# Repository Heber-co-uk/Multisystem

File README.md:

# Multisystem all-in-one console motherboard designed by Heber Ltd. for MiSTer and the DE10-nano FPGA platform

### [Multisystem I/O console motherboard](https://github.com/Heber-co-uk/Multisystem/Multisystem_All_in_One_PCB)
This all in one motherboard (console) is designed by Heber Ltd. and is released as open-source hardware for the MiSTer FPGA community and project. This console style motherboard provides SCART, VGA, Analog and Digital audio outputs, 128MB of SDRAM, SNAC with automatic level-shifters. Multisystem also has a built in 7 port USB 2.0 Hub. HDMI Isolation, fan connections, power switch, Ethernet, 2nd SD CARD interface and a dedicated expansion connector for various cartridges.

### [Multisystem 3D printed enclosure](https://www.printables.com/model/159379-mister-multisystem-v5-2022-classic-gaming-console-)
An open source enclosure is also available  designed for 3D printing (CC-BY-SA-4.0) commercial use license, over on Printables. Various other enclosures, modules, cartridges and expansions are also being made available all the time. Please check back for future updates and new 3D prints. 3D enclosure designed by Richard Horne @RichRap3D for Heber and the Multisystem / MiSTer project.

### Various images of the Multisystem PCB can be found [here](https://github.com/Heber-co-uk/Multisystem/images)

### A comprehensive user manual for the Multisystem can be found [here](https://github.com/Heber-co-uk/Multisystem/Manual)
Please check the manual if you have any questions about assembly and use of the Multisystem or the MiSTer FPGA project.

### [The official RTC daughter board is also supported on the Multisystem](https://github.com/MiSTer-devel/Hardware_MiSTer/tree/master/Addons/RTC)
This board provides real time clock. It's plugged into LTC connector.

### [Please support the MiSTer project and its creators & developers](https://patreon.com/FPGAMiSTer)
Please consider supporting the original creators for MiSTer and any of the FPGA Core developers over on Patreon or anywhere you can support or help them.

### [Alexey Melnikov](https://github.com/sorgelig)
The MiSTer project, electronics hardware, the Linux software and many FPGA cores would not have been possible without the dedicated efforts of the community, past projects like MiST and especially Alexey Melnikov for the porting over to the DE10-nano as MiSTer. Please support the project wherever you can.

### [MiSTer Forum](https://misterfpga.org/)
The MiSTer project forum can be found here.

### [RMC Retro - TheCave]( https://www.rmcretro.com/)
We would like to thank Neil at RMCRetro for the ongoing support of this project and many others for the Retro Gaming, classic computer and Arcade gaming communities. 

### [Heber Ltd.](https://heber.co.uk/) Heber are developing hardware for the Retro Gaming, classic computer and Arcade gaming communities. If you would like to know more, please visit our website or follow us on social media. 

## Notes
The PCB design and schematic is made in Altium, you will need to use Altium Designer v19.0 (or later) in order to view the source files. For convenience, [gerber files (*.zip)]( https://github.com/Heber-co-uk/Multisystem/Multisystem_All_in_One_PCB releases) are also included
and ready to submit to a PCB manufacturer of your choice.

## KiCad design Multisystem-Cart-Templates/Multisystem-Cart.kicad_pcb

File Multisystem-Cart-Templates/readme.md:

# Heber Expansion Cartridge templates

KiCad templates for cartridges for the Multisystem and Multisystem2 / Future Multisystems.

Schematic includes the edge connector with appropriately labelled nets.

PCB includes the edge connector and a board outline.

The Multisystem cartridge also includes a micro USB 3.0 connector, which enables SNAC cartridges to be connected to other MiSTer FPGA systems. On the Multisystem, the V_SNAC signal from the edge connector and power from the USB connector will be at 5V or 3.3V depending on the voltage setting on the Multisystem, but on other MiSTer systems, the voltage from the USB connector is always 5V even when a level shifter is used. VBUS on the edge connector is current-limited 5V from the USB current limiting IC whereas 5V on the edge connector is from the main power input protected only by the main polyfuse. Also note that the SSRX and SSTX pairs are swapped in the micro USB connector; this is because the SSRX pins at the USB end connect to SSTX at the micro USB end of the cable and vice versa.

On Multisystem 2, V_SNAC is fixed at 3.3V and the level of the signals from the system are 3.3V. We recommend designing any SNAC cartridge for 5V devices with on-board level shifters so that they will be compatible with Multisystem and Multisystem 2. The common BSS138 level shifting circuit is sufficient and the pull-ups on the system side should be connected to V_SNAC for correct signal levels on the system side regardless of the position of the 5V/3.3V switch on Multisystem.

If you wish to make your own Cartridges for the Multisystem/Multisystem2, please use this template so they will be compatible.

## Board finish
Never use HASL. Use ENIG.

All official Heber cartridges feature hard gold plating on the edge contacts to improve the long term reliability of the contacts. This is an extra cost option available from most PCB manufacturers and is quite expensive to add if you are ordering prototypes; the boards will of course work without hard gold plating, but standard gold plating will wear off the pads quickly and reduce the reliability over the long term.

## Signals 
 - USB 2.0
 - GPIO Pins (3.3v)
 - Analogue input signals (on Multisystem 2, the ADC is not fitted and these signals are instead routed to the 50W header where the ADC could be connected or the signals could be used for other things)
 - +5V unprotected (2A max)
 - +3.3V unprotected (1A max)
 - GND
 - VBUS (5V protected by USB overcurrent protection IC)
 - V_SNAC (Selectable voltage on the Multisystem board 3.3v or 5v)
 - Full SNAC/USER PORT
 - Digital Audio output
 - PWM Analogue Audio output (unfiltered)
 - RGBHV Analogue video output - various display modes & Standards.
 - Sync On Green signal

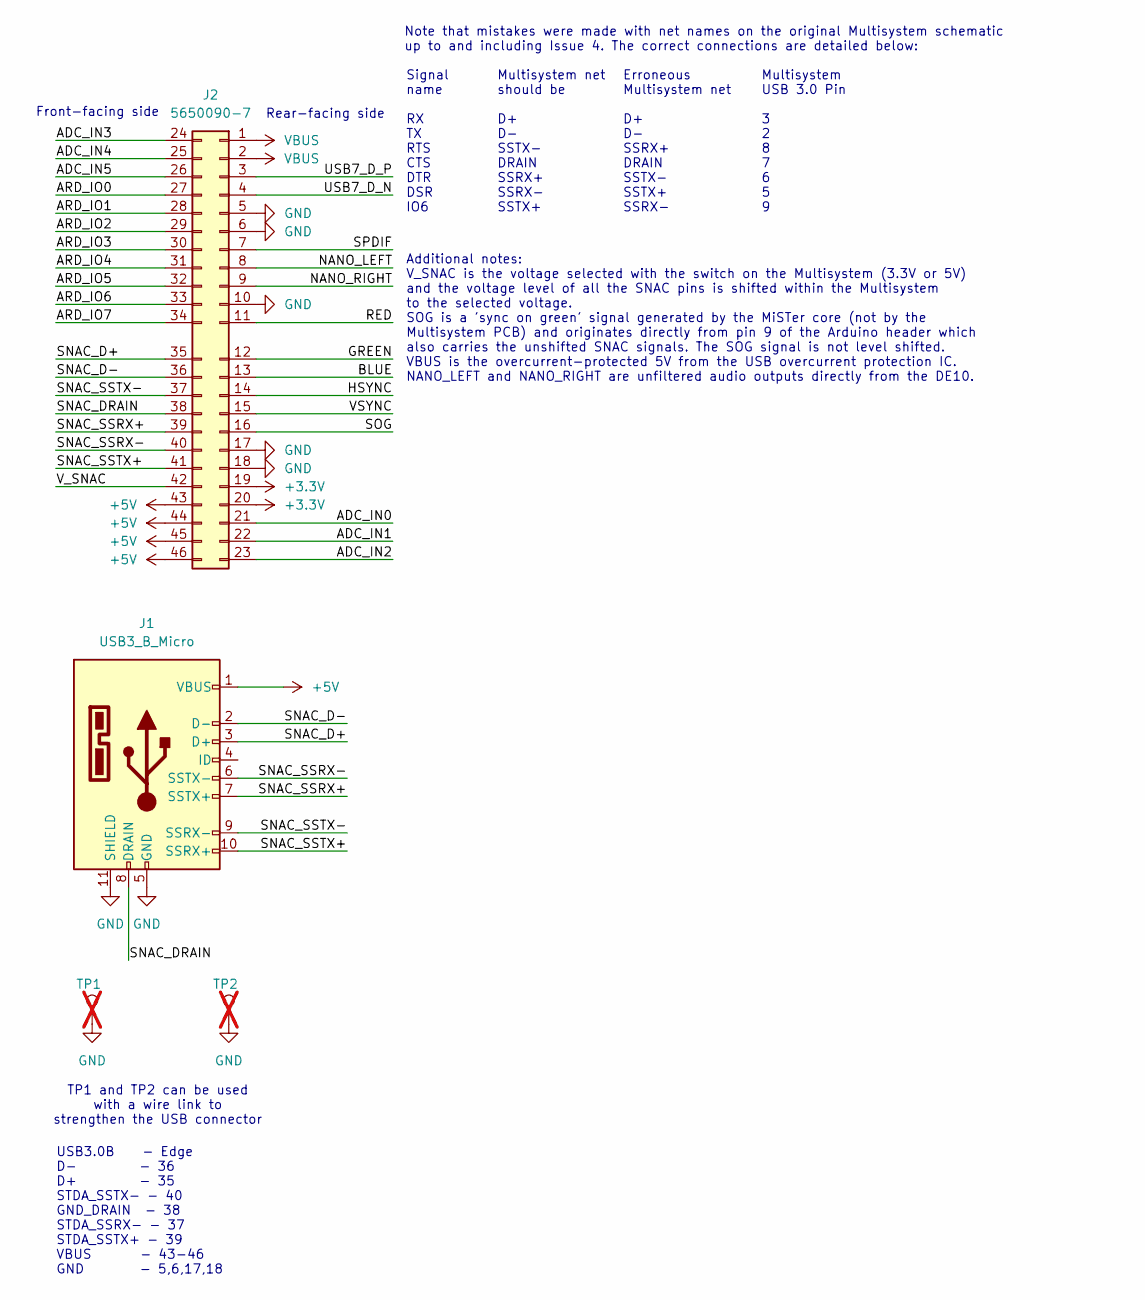
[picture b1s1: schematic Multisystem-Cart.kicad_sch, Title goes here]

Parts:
J1: USB3_B_Micro; CONN-MICRO-USB-3
J2: 5650090-7; PCI_EDGE_AMC_RISER_MULTISYSTEM
TP1, TP2: TestPoint; Pin_D1.0mm_L10.0mm; not fitted

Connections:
+3.3V: J2.19, J2.20
+5V: J1.1 (VBUS), J2.43, J2.44, J2.45, J2.46
/ADC_IN0: J2.21
/ADC_IN1: J2.22
/ADC_IN2: J2.23
/ADC_IN3: J2.24
/ADC_IN4: J2.25
/ADC_IN5: J2.26
/ARD_IO0: J2.27
/ARD_IO1: J2.28
/ARD_IO2: J2.29
/ARD_IO3: J2.30
/ARD_IO4: J2.31
/ARD_IO5: J2.32
/ARD_IO6: J2.33
/ARD_IO7: J2.34
/BLUE: J2.13
/GREEN: J2.12
/HSYNC: J2.14
/NANO_LEFT: J2.8
/NANO_RIGHT: J2.9
/RED: J2.11
/SNAC_D+: J1.3 (D+), J2.35
/SNAC_D-: J1.2 (D-), J2.36
/SNAC_DRAIN: J1.8 (DRAIN), J2.38
/SNAC_SSRX+: J1.7 (SSTX+), J2.39
/SNAC_SSRX-: J1.6 (SSTX-), J2.40
/SNAC_SSTX+: J1.10 (SSRX+), J2.41
/SNAC_SSTX-: J1.9 (SSRX-), J2.37
/SOG: J2.16
/SPDIF: J2.7
/USB7_D_N: J2.4
/USB7_D_P: J2.3
/VSYNC: J2.15
/V_SNAC: J2.42
GND: J1.5 (GND), J1.11 (SHIELD), J2.5, J2.6, J2.10, J2.17, J2.18, TP1.1, TP2.1
VBUS: J2.1, J2.2

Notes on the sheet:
Erroneous Multisystem net D+ D- SSRX+ DRAIN SSTX- SSTX+ SSRX-
USB3.0B - Edge D- - 36 D+ - 35 STDA_SSTX- - 40 GND_DRAIN - 38 STDA_SSRX- - 37 STDA_SSTX+ - 39 VBUS - 43-46 GND - 5,6,17,18
Signal name RX TX RTS CTS DTR DSR IO6
Front-facing side
TP1 and TP2 can be used with a wire link to strengthen the USB connector
Multisystem USB 3.0 Pin 3 2 8 7 6 5 9
Multisystem net should be D+ D- SSTX- DRAIN SSRX+ SSRX- SSTX+
Note that mistakes were made with net names on the original Multisystem schematic up to and including Issue 4. The correct connections are detailed below:
Rear-facing side
Additional notes: V_SNAC is the voltage selected with the switch on the Multisystem (3.3V or 5V) and the voltage level of all the SNAC pins is shifted within the Multisystem to the selected voltage. SOG is a 'sync on green' signal generated by the MiSTer core (not by the Multisystem PCB) and origin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

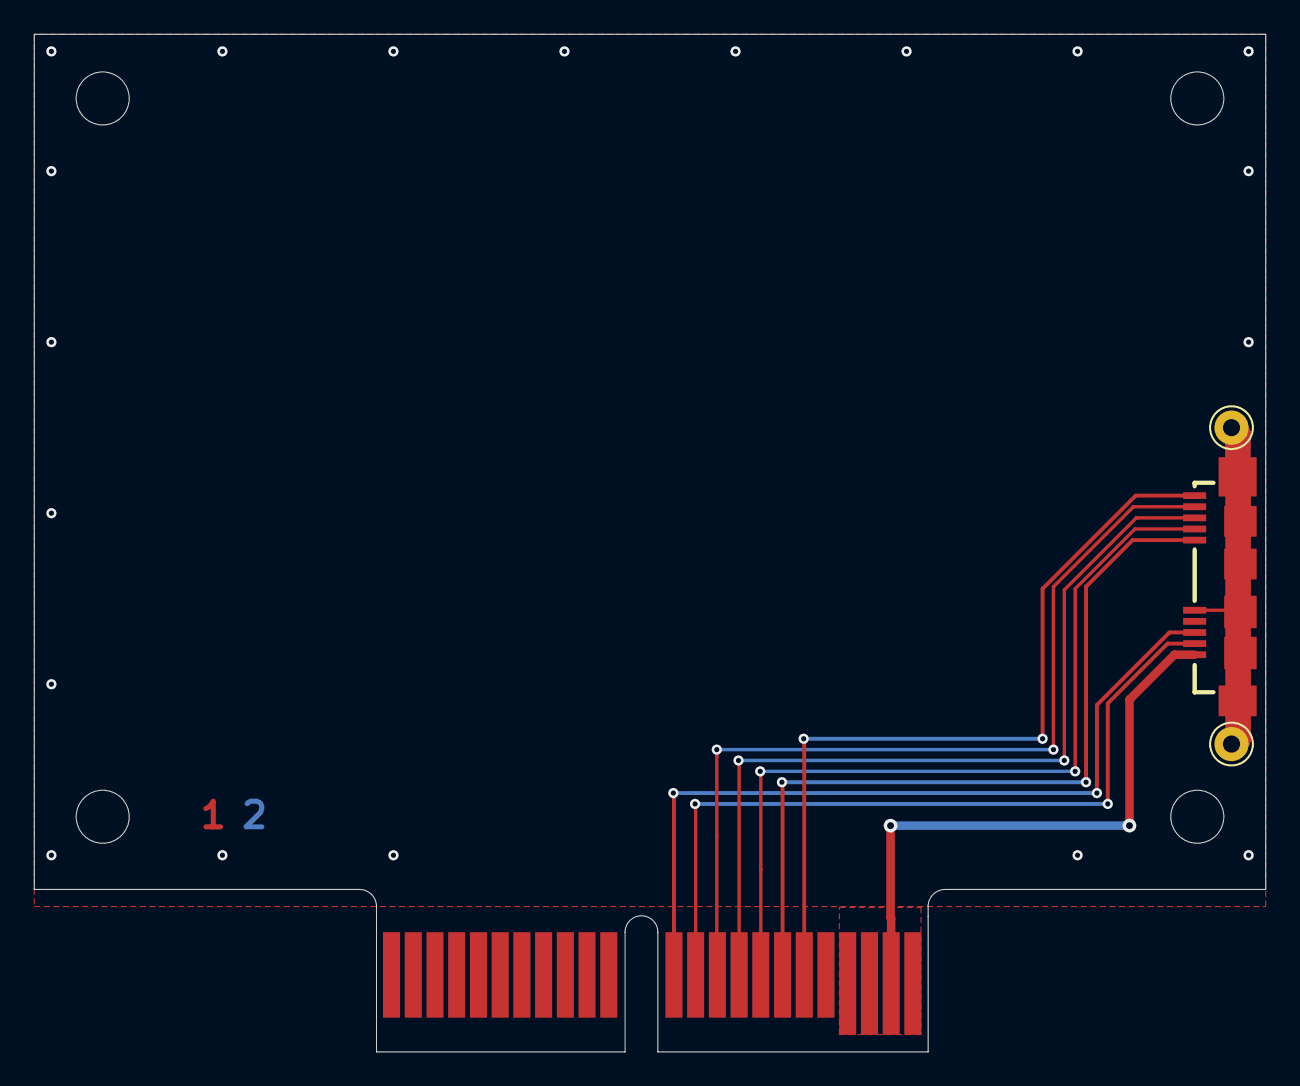
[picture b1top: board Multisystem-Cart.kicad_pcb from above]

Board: 2 copper layers, 72.0 x 59.5 mm, 4 parts (1 on the bottom side), 11 nets.

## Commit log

2023-06-20 Add files via upload
    Production release of Multisystem Console motherboard for MiSTer - (23005-3) Issue 3 - 2023
    Full open-source release for the community.
2024-12-06 KiCad template files for Multisystem1/2 Cartridges
    Added Multisystem & Multisystem 2 KiCad Cartridge PCB and Schematic templates for designing your own cartridge PCB's for MultisystemFPGA
2025-07-15 Move cart templates to separate folder
2025-07-15 Add template PDF outputs
2025-09-30 Clarify cartridge connector descriptions
